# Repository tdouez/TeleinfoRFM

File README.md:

//--------------------------------------------------------------------
//   __|              _/           _ )  |
//   _| |  |   ` \    -_)   -_)    _ \  |   -_)  |  |   -_)
//  _| \_,_| _|_|_| \___| \___|   ___/ _| \___| \_,_| \___|
//--------------------------------------------------------------------
# TeleinfoRFM

Interface Téléinfo pour compteur Linky avec MySensors - version compatible modes historique et standard 

Projet utilisant un Arduino Pro mini et un module RFM95w

- Description disponible sur http://fumeebleue.fr

------------------------------------------------------------------------------------
Code mise à disposition selon les termes de la Licence Creative Commons Attribution
Pas d’Utilisation Commerciale.
Partage dans les Mêmes Conditions 4.0 International.
------------------------------------------------------------------------------------

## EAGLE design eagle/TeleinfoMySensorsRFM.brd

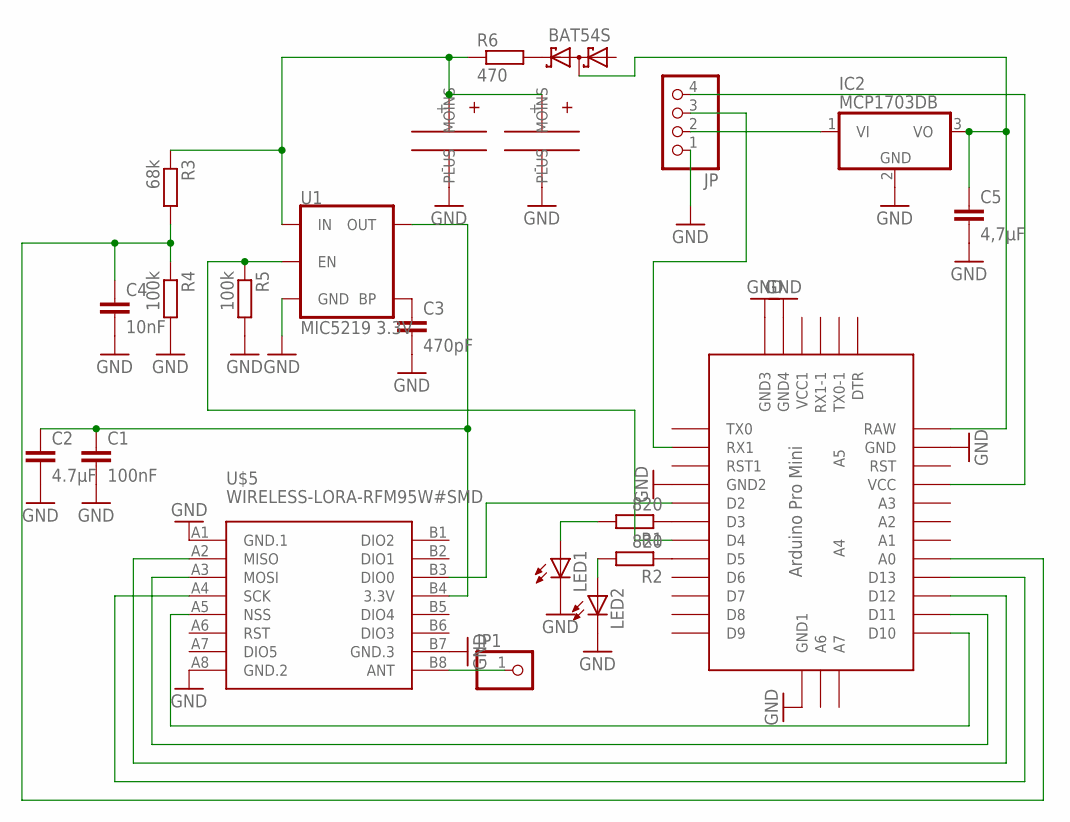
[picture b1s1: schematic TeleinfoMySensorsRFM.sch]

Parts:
C1: 100nF; C1206
C2: 4.7µF; C1210
C3: 470pF; C1206
C4: 10nF; C1206
C5: 4,7µF; C1210
D3: BAT54S; SOT23
IC2: MCP1703DB; SOT223
JP: PINHD-1X4; 1X04
JP1: PINHD-1X1; 1X01
LED1, LED2: LED3MM
R1, R2: 820; M1206
R3: 68k; M1206
R4, R5: 100k; M1206
R6: 470; M1206
U1: MIC5219 3.3V; SOT23-5
U$1: ABK-PRO-MINI
U$2, U$6: SUPERCAPA10
U$5: WIRELESS-LORA-RFM95W#SMD

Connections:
GND: C1.2, C2.2, C3.2, C4.2, C5.2, IC2.2 (GND), JP.1, LED1.K (C), LED2.K (C), R4.2, R5.2, U1.2 (GND), U$1.GND, U$1.GND1 (GND2), U$1.GND2 (GND3), U$1.GND3 (GND4), U$1.GND4 (GND1), U$2.- (MOINS), U$5.A1 (GND.1), U$5.A8 (GND.2), U$5.B7 (GND.3), U$6.- (MOINS)
unnamed: JP1.1, U$5.B8 (ANT)
unnamed: LED2.A, R2.2
unnamed: U$1.D12, U$5.A2 (MISO)
unnamed: R1.1, U$1.D3
unnamed: IC2.1 (VI), JP.2
unnamed: U$1.D11, U$5.A3 (MOSI)
unnamed: U$1.D13, U$5.A4 (SCK)
unnamed: U$1.D10, U$5.A5 (NSS)
unnamed: R2.1, U$1.D5
unnamed: U$1.D2, U$5.B3 (DIO0)
unnamed: LED1.A, R1.2
unnamed: JP.3, U$1.RX1
unnamed: C3.1, U1.4 (BP)
unnamed: C5.1, D3.3 (C1A2), IC2.3 (VO), U$1.RAW
unnamed: R5.1, U1.3 (EN), U$1.D4
unnamed: C4.1, R3.2, R4.1, U$1.A0
unnamed: C1.1, C2.1, U1.5 (OUT), U$5.B4 (3.3V)
unnamed: JP.4, U$1.VCC
unnamed: D3.2 (C2), R6.2
unnamed: R3.1, R6.1, U1.1 (IN), U$2.+ (PLUS), U$6.+ (PLUS)

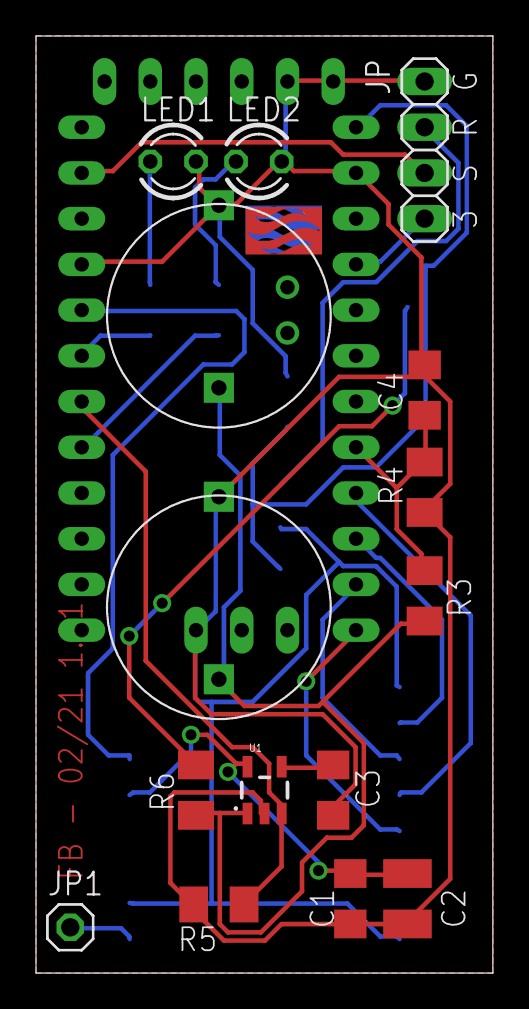
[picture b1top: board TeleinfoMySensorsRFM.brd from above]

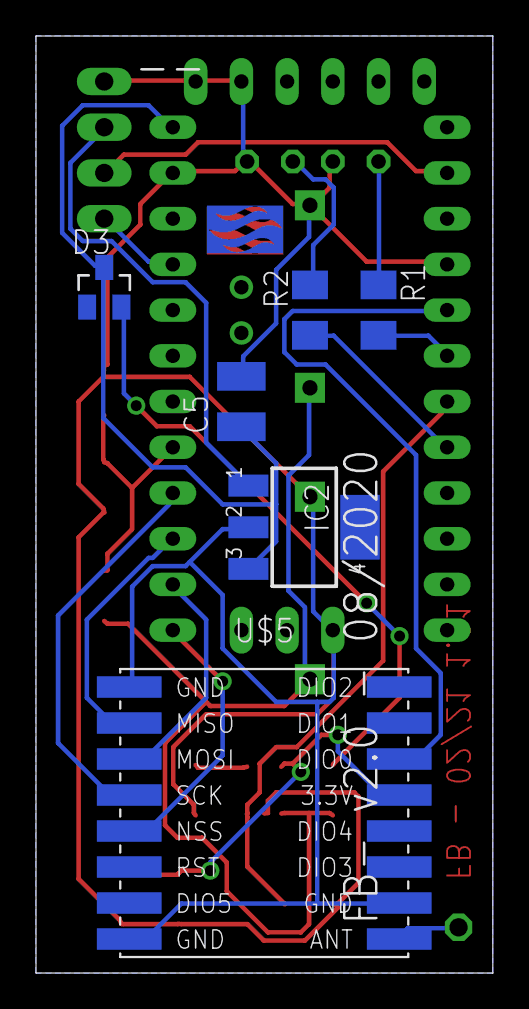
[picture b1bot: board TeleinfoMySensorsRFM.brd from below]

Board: 2 copper layers, 25.4 x 52.1 mm, 24 parts (7 on the bottom side), 21 nets.

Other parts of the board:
U$3, U$4: FB

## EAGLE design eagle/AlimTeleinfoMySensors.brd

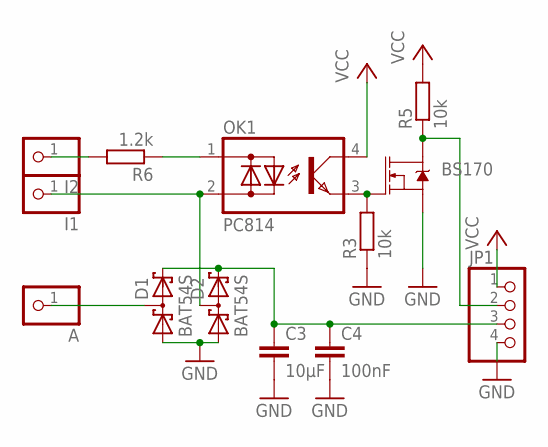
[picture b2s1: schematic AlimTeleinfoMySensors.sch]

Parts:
A: PINHD-1X1; 1X01
BS170: MOSFET-NCH-BSS138; SOT23-3
C3: 10µF; C1210
C4: 100nF; C1206
D1, D2: BAT54S; SOT23
I1, I2: PINHD-1X1; 1X01
JP1: PINHD-1X4; 1X04
OK1: PC814; DIL04
R3, R5: 10k; M1206
R6: 1.2k; M1206

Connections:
GND: BS170.2 (S), C3.2, C4.2, D1.1 (A1), D2.1 (A1), JP1.4, R3.1
unnamed: I2.1, R6.2
unnamed: D2.3 (C1A2), I1.1, OK1.2 (AC2)
unnamed: BS170.3 (D), JP1.2, R5.1
unnamed: C3.1, C4.1, D1.2 (C2), D2.2 (C2), JP1.3
unnamed: OK1.1 (AC1), R6.1
unnamed: BS170.1 (G), OK1.3 (E), R3.2
unnamed: A.1, D1.3 (C1A2)
VCC: JP1.1, OK1.4 (C), R5.2

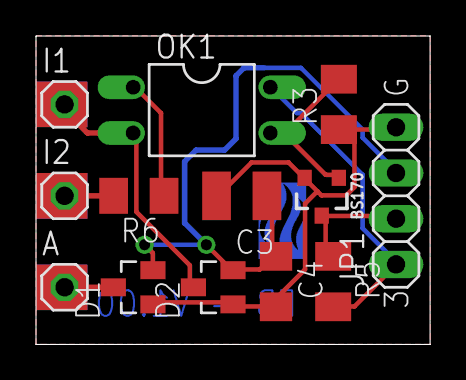
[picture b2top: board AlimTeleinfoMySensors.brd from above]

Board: 2 copper layers, 21.9 x 17.1 mm, 14 parts (0 on the bottom side), 9 nets.

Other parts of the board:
U$1: FB

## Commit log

2021-06-29 V1.01
    V1.01
2021-11-21 V1.0.3
    Correction bug sur mode triphasé et producteur
2021-12-23 V2.00
    Utilisation de la librairie libTeleinfo (https://github.com/hallard/LibTeleinfo) et chg protocole vers GW
    Compatible uniquement avec la version logicielle de la gateway > V2.x
2021-12-27 V2.0.1
    Fix bug aléatoire, blocage envoi data
2022-01-08 v2.02
    Optimisation utilisation mémoire et emissions datas. Ajout détection vitesse TIC
2022-01-11 V2.0.3
    Suppression warning et modif gestion timeout vitesse TIC
2022-01-25 2.0.4
    Correction sur détection TIC historique
2022-06-26 V2.0.5
    Optimisation mémoire
2022-09-27 V2.0.6
    Correction sur détection TIC standard
2023-03-06 V2.0.7
    Ajout indication réception TIC et optimisation mémoire
2023-03-30 v2.0.8
    Correction blocage aléatoire module, frequence maj 15 à 20s, clignotement durant charge condo
2023-05-04 v2.0.9
    Amélioration détection mode TIC historique/standard
2023-06-03 V2.0.10
    Correction detection TIC historique
2025-01-03 V2.0.11
    Ajout compatibilité avec le Arduino Pro Micro

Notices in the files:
parts and their libraries:
SparkFun-DiscreteSemi: Licensing: Creative Commons ShareAlike 4.0 International - https://creativecommons.org/licenses/by-sa/4.0
diy-modules: Released under the Creative Commons Attribution 4.0 International License: http://creativecommons.org/licenses/by/4.0
